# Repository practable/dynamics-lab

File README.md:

# dynamics lab

Dynamics experiment to investigate resonance of a mass-beam system. Free decay or driven oscillations can be measured. Frequency of driven oscillation can be controlled using a stepper motor and the uStepper s32 driver board. 

Initial prototype designed as part of an undergraduate student project in the School of Engineering, University of Edinburgh. That design was modified and implemented in this remote laboratory for the Structural Mechanics and Dynamics 3 course in the same department. The experiments are on public display in the School of Engineering:

<div>

</div>

If you are interested in adopting or designing a new remote laboratory based on this, or any, practable remote lab then please visit [www.practable.io](http://www.practable.io)

# Contents

Details of the hardware, firmware and UI can be found in the following directories:

- [fw](./fw/README.md)
- [hw](./hw/README.md)
- [ui](./ui/README.md)
- [sbc](./sbc/README.md)

# Activities

- Free decay in a mass-spring system
- Damping ratio of free decay
- Resonance curve for driven oscillations
- Phase lag between driver and oscillator

## Version History

| Date | Version      | Update notes    |
| ------| ------------- | ------------- |
| September 2025 | v1.0           | Initial production release of dynamics lab |

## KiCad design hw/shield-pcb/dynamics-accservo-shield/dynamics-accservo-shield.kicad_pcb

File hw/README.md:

# hardware

## Production Serial Numbers

- ACC000
- ACC001-017

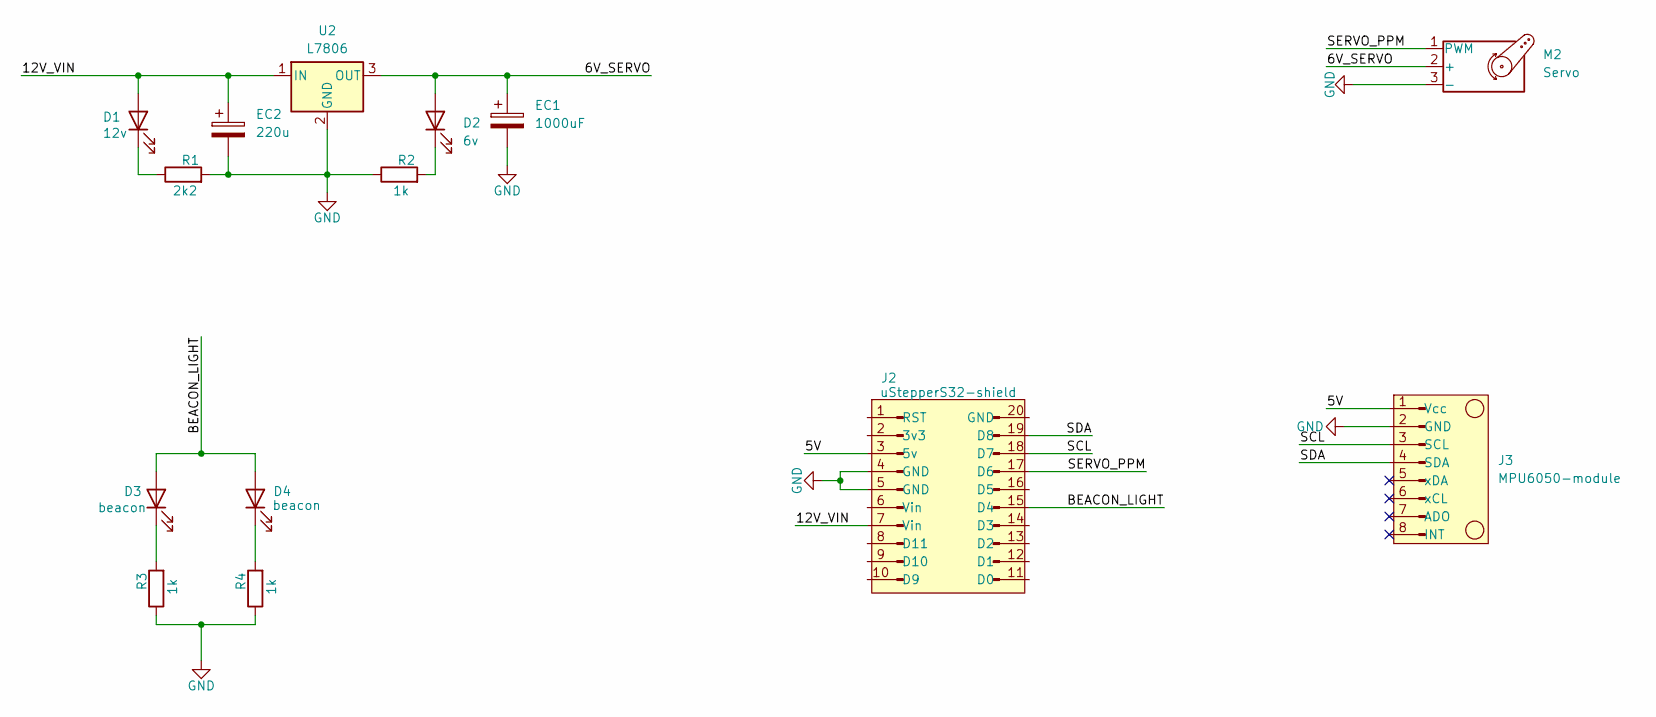
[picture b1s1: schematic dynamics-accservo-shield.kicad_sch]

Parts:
D1: 12v; D_0805_2012Metric_Pad1.15x1.40mm_HandSolder; JLCpart C84261
D2: 6v; D_0805_2012Metric_Pad1.15x1.40mm_HandSolder; JLCpart C84259
D3: beacon; D_0805_2012Metric_Pad1.15x1.40mm_HandSolder; JLCpart C94741
D4: beacon; LED_D5.0mm
EC1: 1000uF; CP_Radial_D13.0mm_P5.00mm; JLCpart C134726
EC2: 220u; CP_Elec_6.3x7.7; JLCpart C3342
J2: uStepperS32-shield; uSteppers32-dev-sheild
J3: MPU6050-module; MPU6050-acc-module
M2: Servo; servo-PinHeader_1x03_P2.54mm_Vertical
R1: 2k2; R_0805_2012Metric_Pad1.20x1.40mm_HandSolder; JLCpart C218388
R2, R3, R4: 1k; R_0805_2012Metric_Pad1.20x1.40mm_HandSolder; JLCpart C218388
U2: L7806; TO-263-2; JLCpart C26467

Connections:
/5V: J2.3 (5v), J3.1 (Vcc)
/6V_SERVO: D2.2 (A), EC1.1, M2.2 (+), U2.3 (OUT)
/12V_VIN: D1.2 (A), EC2.1, J2.7 (Vin), U2.1 (IN)
/BEACON_LIGHT: D3.2 (A), D4.2 (A), J2.15 (D4)
/SCL: J2.18 (D7), J3.3 (SCL)
/SDA: J2.19 (D8), J3.4 (SDA)
/SERVO_PPM: J2.17 (D6), M2.1 (PWM)
GND: EC1.2, EC2.2, J2.4 (GND), J2.5 (GND), J3.2 (GND), M2.3 (-), R1.2, R2.1, R3.1, R4.1, U2.2 (GND)
unnamed: D1.1 (K), R1.1
unnamed: D2.1 (K), R2.2
unnamed: D3.1 (K), R3.2
unnamed: D4.1 (K), R4.2

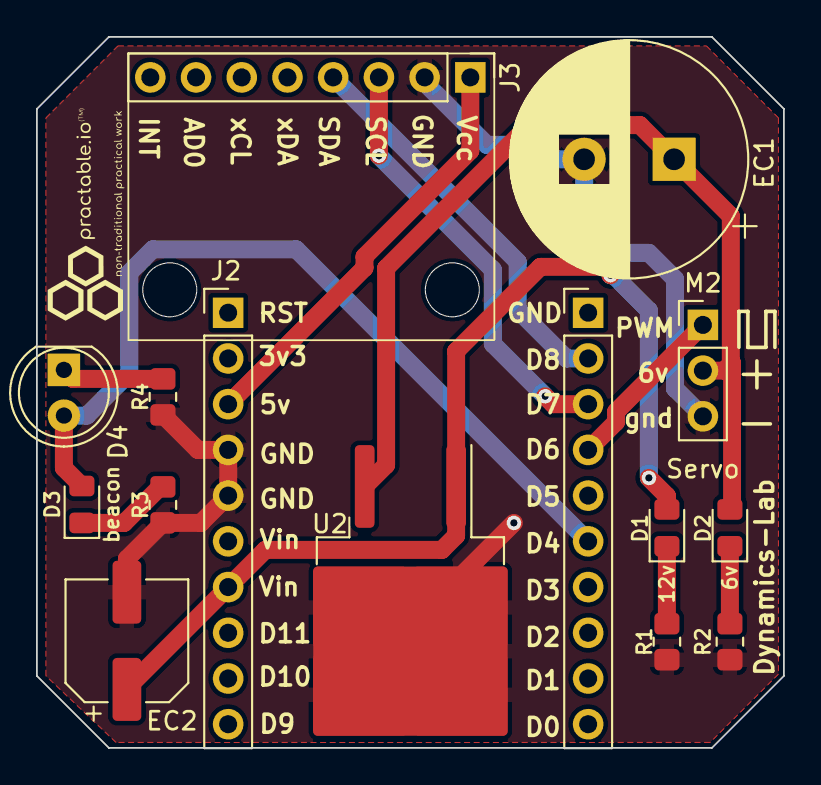
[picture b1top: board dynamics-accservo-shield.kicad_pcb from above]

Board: 2 copper layers, 41.5 x 39.5 mm, 14 parts (0 on the bottom side), 12 nets.

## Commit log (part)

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2024-12-02 Initialize develop
2024-12-02 Started developing firmware
2024-12-03 dynamics lab test
2024-12-03 added gyro test demo
2024-12-12 homing function hall sensor working
2024-12-12 tried to make more robust, maybe less robust but more interesting
2024-12-18 added stall limits
2024-12-18 bfdf
2025-01-23 deleted unknown files
2025-01-23 added test functions wor
2025-02-04 servo example with new library
2025-02-05 trying to compile for AVR, then find libs for STM32
2025-02-06 software first version is somewhat functional
2025-02-06 sort of working but not well
2025-02-07 program more complete but stepper not working after startup
2025-02-07 updating alot of code commented out but i dont think the code is the probl;em
2025-02-07 version working better, think it was the servo library that was causing issues
2025-02-07 almost all there apart from servo
2025-02-10 Dynamics Firmware V0.0.0 Alpha for prototype working
2025-02-10 added V0.1.0 with standardised command structure
    `{"set":"{CMD},"to":{VALUE}"}`
2025-02-11 finished version V0.1.1 -> JSONified all debug messages
2025-02-11 ui (add): initial commit of new dynamics lab default interface
2025-02-11 ui (update): minor changes to logging config and package to remove issues with dependencies
2025-02-11 ControlPanel (add): started developing the control panel component
2025-02-17 control panel component added and development started
2025-02-18 ControlPanel (update): control panel component v0.1 complete
2025-02-21 added data recorder and graph components
2025-02-24 ui (update): add acceleration and driving force plot in driven mode
2025-02-25 ui (update): add a data panel component for outputting calculated values
2025-02-26 ui (update): update to DataPanel component to display max and rms average values for any selected dataset
2025-02-26 ui (fix): add components in mobile version
2025-02-27 big updates
2025-02-28 fixed sampling issues and accellerometer
2025-02-28 encoder now has absolute position
2025-02-28 added guards for sample and print rate to prevent errors if set incorrectly
2025-03-03 Major updates
2025-03-03 updated with working HOME function. EEPROM left half implemented for later use
2025-03-03 Changed reference to forked uStepperS32 library
2025-03-04 ui (update): now uses array of values from firmware and set home updated
2025-03-04 ui (update): updates to style og DataPanel, layout of second row on App, remove pos from DataPanel, add units to chart, selected dataset updates with new recorded dataset
2025-03-05 Removed print timing and made print dependent on collecting required number of samples
2025-03-05 changed home state to non-blocking
2025-03-07 ControlPanel.vue (fix): remove call to set sampling rate on data connection open, this may have been causing the stream to stop
2025-03-28 started PCB dev
2025-03-28 added PCB design
2025-04-03 finished hardware dev
2025-05-30 graph (feat): add showLine
2025-06-02 WebcamStream (feat): add options to update smoothie streams
2025-06-03 Graph (fix): add id to function dataset, bringing it in line with the recorded data sets, to stop error after function was plotted
2025-06-03 Graph (fix): only show secondary y axis if a dataset has been recorded that is associated with that axis
2025-06-04 ui (update): v0.9 ready for final testing with prototype
2025-06-05 ui (update): hardware configuration added to ui from config file
2025-06-05 ui (update): enable dragging of popup help dialogs
2025-06-05 ui (update): minor update to popuphelp component
2025-06-05 ui (update): plotting functions are now movable
2025-06-11 updates for prototype
2025-06-12 sdfcsd
2025-06-12 adjusted sample rate for more samples, removed or statement from sampling timing function
2025-06-19 small updates to firmware
2025-06-24 ui (feat): add control panel buttons for small increments and decrements of frequency
2025-06-24 ui (feat): add driving frequency in data download
2025-06-24 ui (update): add mode and driving frequency to data display on UI
2025-06-24 corrected calibration algorithm
2025-06-24 ui/default (fix): display of driving freq was based on incorrect name for driven state, also added spacing to maintain correct format on table whether driving freq is displayed or not
2025-06-24 ui/default (fix): fix output of driving frequency in CSV to only have 2 decimal places
2025-06-26 ui/default (fix): fix issue when attempting to plot undriven and then driven on the same graph given that undriven only creates one graph dataset but driven creates two. Solution was to plot position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
2025-07-01 Graph (fix): add line to function plots and change name of position plot to force
2025-07-07 ui/default (update): remove gyro data, automatically record on ping start
2025-07-07 ui/default (fix): minor fix to data panel span of lines across full table in mode undriven
2025-07-10 working on production firmware
2025-07-11 stall detection working
2025-07-11 updated JSON messenger with modifications from Dynamics & improved debug options
2025-07-11 fixed brake and freewheel states, both now stop motor action
2025-07-11 added timeout that applys FREEWHEEL brake mode to cut down motor heating
2025-07-11 finished goto state, now fully functional.
2025-07-14 move (angle) command added, goto and home algorithms improved
2025-07-14 added all state machine items for calibration, states are not functional yet
2025-07-14 updates to secretObject
2025-07-15 Dynamics V1.0.0 firmware completed
2025-07-15 small updates to working version
2025-07-15 small updates
2025-07-15 started work on demo mode
2025-07-16 added to demo mode
2025-07-16 demo mode
2025-07-18 updates to demo feature
2025-07-21 JSON safed outputs
2025-07-25 organised files & folders
2025-07-29 Big changes half due to changing laptop
2025-07-30 major updates, bug fix, fixed accelleration values, stripped old error system
    big updates to production ready firmware
2025-08-13 ui/ControlPanel (fix): have fixed issue with duplicating data when a reconnection occurs. Whilst the streams were being correctly reconnected to, the UI was creating a new websocket but maintaining t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
2025-08-14 ui/default/NavigationBar (update): add experiment ID to nav bar from config file
2025-08-14 ui/default/Graph (fix): fix precision on graph axes to 2, stopping large numbers of dp display
2025-09-12 ui/default (fix): allow 5000 data points to be graphed, matching the number that can be recorded
2025-09-12 ui/analytics (add): add new analytics version of UI
2025-09-15 updated Gyro Acc Max from 4G to 8G. Updated to V 1.2.1
2025-09-23 ui (fix): built for production
2025-09-23 README (update): update readme(s) for production
2025-09-23 README (fix): add possible activities and update images
2025-09-24 ui/gamified (add): initial commit of files for gamified UI version - identical to analytics except with updated production build paths
2025-09-24 ui/gamified (update): initial commit of achievements component
2025-10-01 ui/gamified (fix): add new achievements
2025-10-01 ui/gamified (update): added gamepad component and started development of features
2025-10-02 ui/gamified/Gamepad.vue (fix): updated gamepad to almost fully functional, need to test with remote lab
2025-10-03 ui/gamified (fix): v0.9 ready for testing
2025-10-03 ui/gamified (fix): update vibration control weak and strong magnitude to use the first value in the acceleration array
2025-10-03 ui/gamified (fix): minor layout changes and removed temp gamepad button display
2025-10-03 ui/gamified (fix): above 2g maxes out vibration actuator
2025-10-09 ui/gamified (fix): add navigation control using bumper buttons
2025-10-09 ui/gamified (update): enable navigation and input with the gamepad on all input components
2025-10-14 ui/gamified/Gamepad.vue (update): add button mapping for different controllers and allow for different controls to have physical buttons as axes rather than buttons
2025-10-14 ui/README (fix): merged
2026-06-16 Gamepad.vue (update): minor update to output gamepad id
2026-06-16 remove gamified dist files
2026-06-17 ui-video-only (add): video ui added for demonstration purposes
